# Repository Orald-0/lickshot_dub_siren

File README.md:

caga solo il proj DA SBROGLIARE  il resto é vecchio

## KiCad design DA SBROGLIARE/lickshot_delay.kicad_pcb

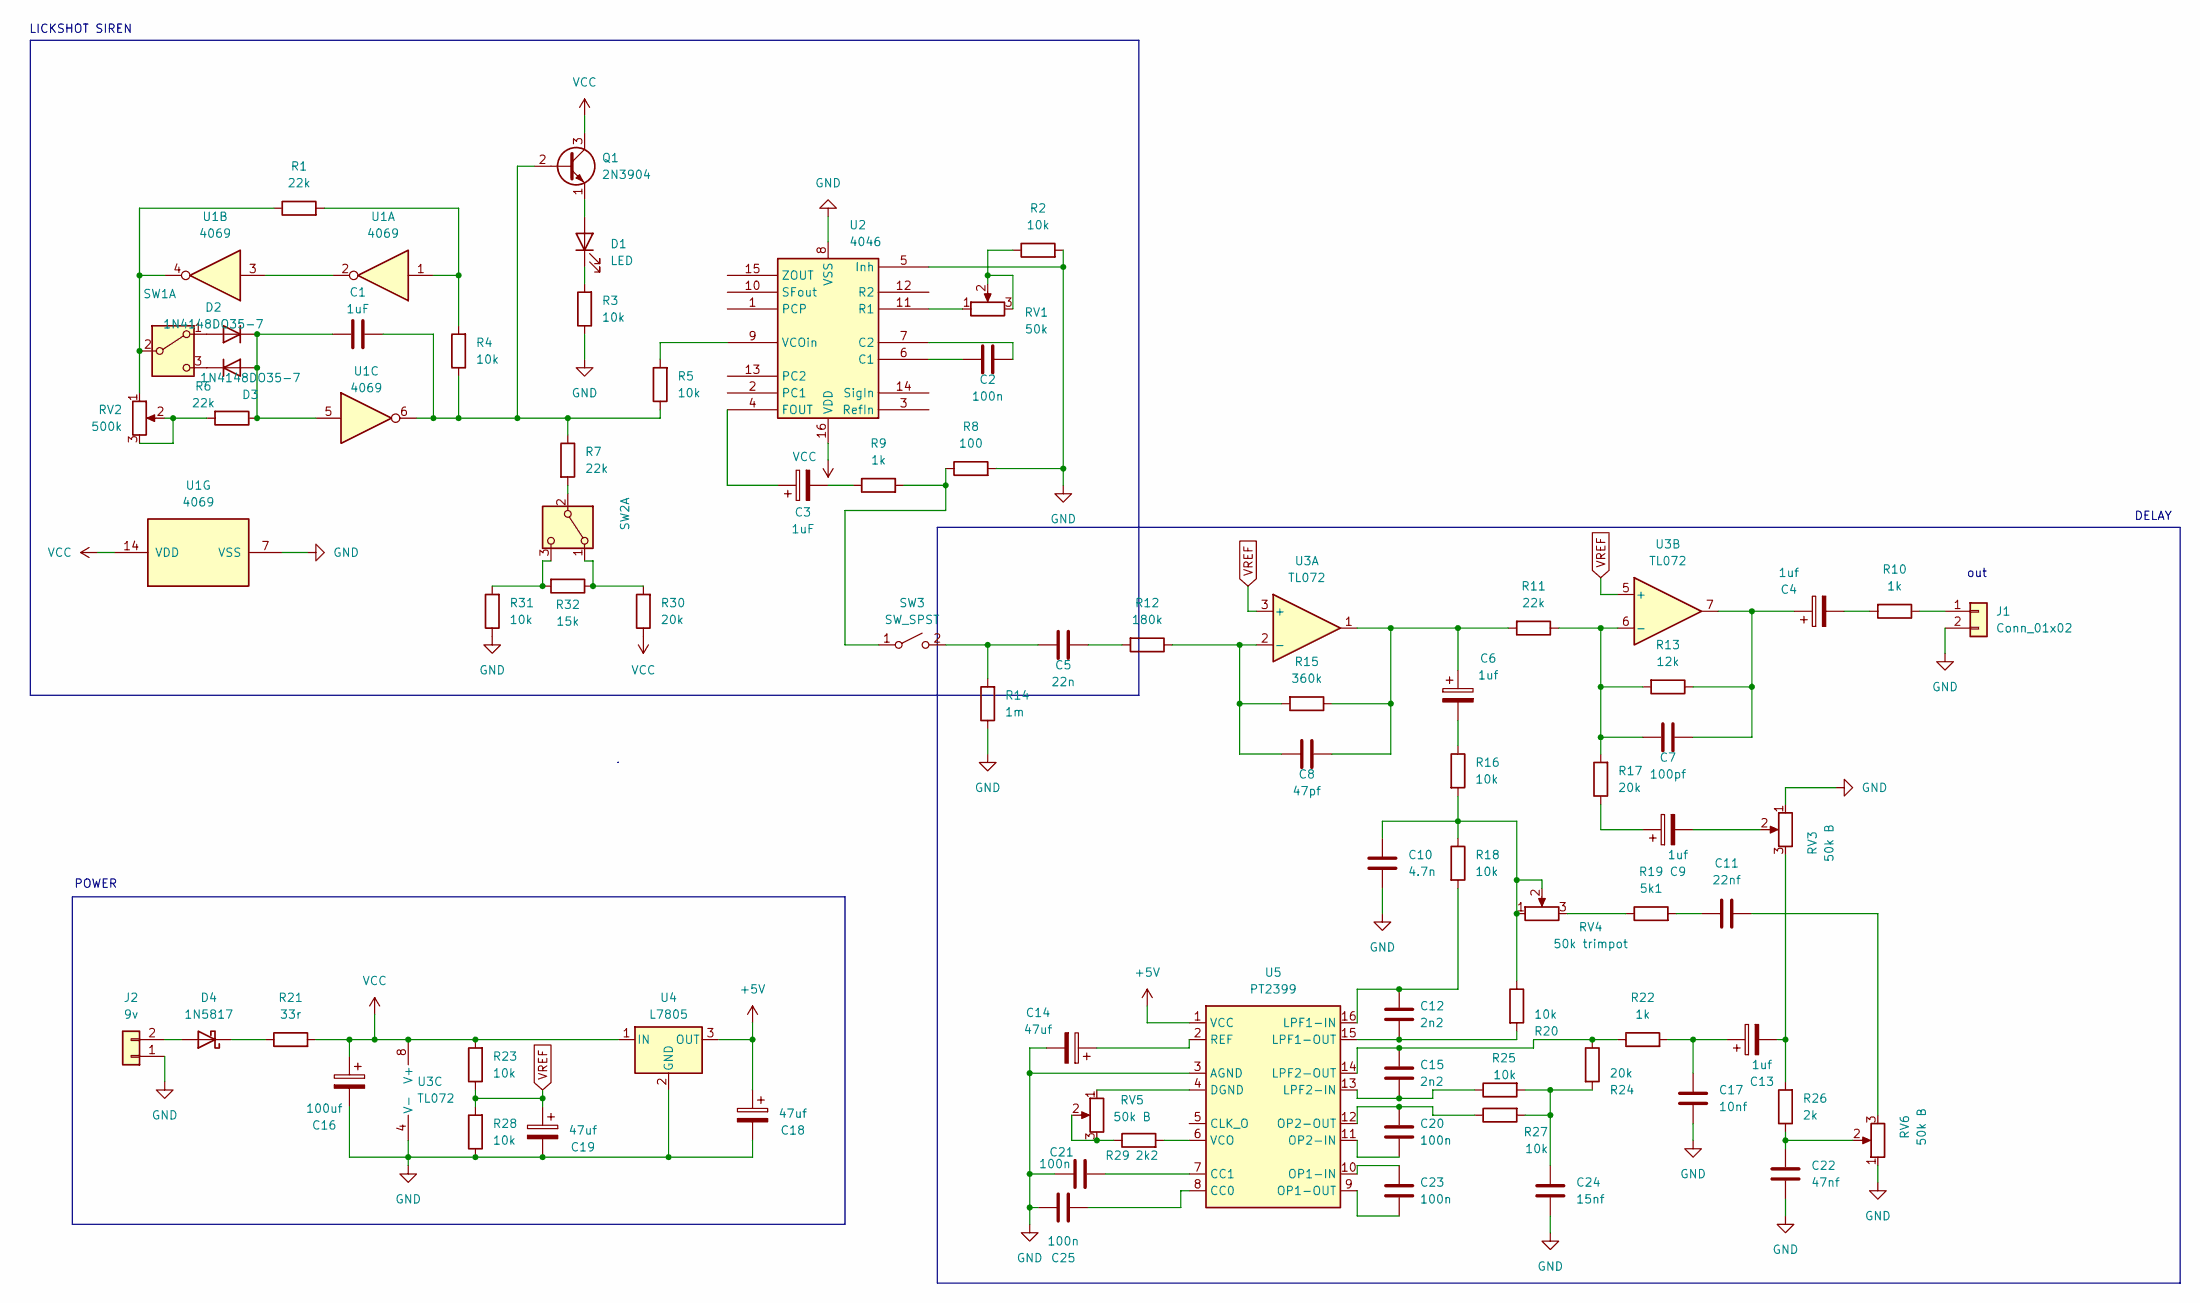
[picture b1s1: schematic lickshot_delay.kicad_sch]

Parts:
C1: 1uF; C__FILM_BOX_Rect_L7.2mm_W3mm_P5mm
C2, C20, C21, C23, C25: 100n; C__FILM_BOX_Rect_L7.2mm_W3mm_P5mm
C3: 1uF; CP_Electro_Radial_D5.0mm_P2.50mm
C4, C6, C9, C13: 1uf; CP_Electro_Radial_D5.0mm_P2.50mm
C5: 22n; C__FILM_BOX_Rect_L7.2mm_W3mm_P5mm
C7: 100pf; C__FILM_BOX_Rect_L7.2mm_W3mm_P5mm
C8: 47pf; C__FILM_BOX_Rect_L7.2mm_W3mm_P5mm
C10: 4.7n; C__FILM_BOX_Rect_L7.2mm_W3mm_P5mm
C11: 22nf; C__FILM_BOX_Rect_L7.2mm_W3mm_P5mm
C12, C15: 2n2; C__FILM_BOX_Rect_L7.2mm_W3mm_P5mm
C14, C18, C19: 47uf; CP_Electro_Radial_D5.0mm_P2.50mm
C16: 100uf; CP_Electro_Radial_D5.0mm_P2.50mm
C17: 10nf; C__FILM_BOX_Rect_L7.2mm_W3mm_P5mm
C22: 47nf; C__FILM_BOX_Rect_L7.2mm_W3mm_P5mm
C24: 15nf; C__FILM_BOX_Rect_L7.2mm_W3mm_P5mm
D1: LED; LED_D5.0mm
D2, D3: 1N4148DO35-7; DIODE_DO-35_SOD27_P7.62mm_Horizontal
D4: 1N5817; DIODE_DO-35_SOD27_P7.62mm_Horizontal
J1: Conn_01x02; SolderWire-0.5sqmm_1x02_P4.6mm_D0.9mm_OD2.1mm
J2: 9v; SolderWire-0.5sqmm_1x02_P4.6mm_D0.9mm_OD2.1mm
Q1: 2N3904; TO-92_Inline
R1, R6, R7, R11: 22k; RES_0.25watt_L3.6mm_D1.6mm_P7.62mm_Horizontal
R2, R3, R4, R5, R16, R18, R20, R23, R25, R27, R28, R31: 10k; RES_0.25watt_L3.6mm_D1.6mm_P7.62mm_Horizontal
R8: 100; RES_0.25watt_L3.6mm_D1.6mm_P7.62mm_Horizontal
R9, R10, R22: 1k; RES_0.25watt_L3.6mm_D1.6mm_P7.62mm_Horizontal
R12: 180k; RES_0.25watt_L3.6mm_D1.6mm_P7.62mm_Horizontal
R13: 12k; RES_0.25watt_L3.6mm_D1.6mm_P7.62mm_Horizontal
R14: 1m; RES_0.25watt_L3.6mm_D1.6mm_P7.62mm_Horizontal
R15: 360k; RES_0.25watt_L3.6mm_D1.6mm_P7.62mm_Horizontal
R17, R24, R30: 20k; RES_0.25watt_L3.6mm_D1.6mm_P7.62mm_Horizontal
R19: 5k1; RES_0.25watt_L3.6mm_D1.6mm_P7.62mm_Horizontal
R21: 33r; RES_0.25watt_L3.6mm_D1.6mm_P7.62mm_Horizontal
R26: 2k; RES_0.25watt_L3.6mm_D1.6mm_P7.62mm_Horizontal
R29: 2k2; RES_0.25watt_L3.6mm_D1.6mm_P7.62mm_Horizontal
R32: 15k; RES_0.25watt_L3.6mm_D1.6mm_P7.62mm_Horizontal
RV1: 50k; SolderWire-0.5sqmm_1x03_P4.6mm_D0.9mm_OD2.1mm
RV2: 500k; SolderWire-0.5sqmm_1x03_P4.6mm_D0.9mm_OD2.1mm
RV3, RV5, RV6: 50k B; SolderWire-0.5sqmm_1x03_P4.6mm_D0.9mm_OD2.1mm
RV4: 50k trimpot; Potentiometer_Piher_PT-10-V10_Vertical
SW1, SW2: SW_DPDT_x2; SolderWire-0.5sqmm_1x03_P4.6mm_D0.9mm_OD2.1mm
SW3: SW_SPST; SolderWire-0.5sqmm_1x02_P4.6mm_D0.9mm_OD2.1mm
U1: 4069; DIP-14_W7.62mm
U2: 4046; DIP-16_W7.62mm
U3: TL072; DIP-8_W7.62mm
U4: L7805; TO-220-3_Vertical
U5: PT2399; DIP-16_W7.62mm

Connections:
+5V: C18.1, U4.3 (OUT), U5.1 (VCC)
GND: C10.2, C14.2, C16.2, C17.1, C18.2, C19.2, C21.1, C22.2, C24.1, C25.1, J1.2, J2.1, R2.2, R3.1, R8.2, R14.1, R28.1, R31.1, RV3.1, RV6.1, U1.7 (VSS), U2.5 (Inh), U2.8 (VSS), U3.4 (V-), U4.2 (GND), U5.3 (AGND)
unnamed: C3.2, R9.1
unnamed: C4.1, C7.2, R13.1, U3.7
unnamed: C4.2, R10.2
unnamed: C5.2, R12.2
unnamed: C6.1, C8.2, R11.2, R15.1, U3.1
unnamed: C6.2, R16.1
unnamed: C9.1, R17.1
unnamed: C9.2, RV3.2
unnamed: C10.1, R16.2, R18.1, R20.1, RV4.1, RV4.2
unnamed: C11.1, R19.2
unnamed: C11.2, RV6.3
unnamed: C13.1, C17.2, R22.2
unnamed: C13.2, R26.2, RV3.3
unnamed: C22.1, R26.1, RV6.2
unnamed: C24.2, R24.2, R25.2, R27.2
unnamed: D1.2 (A), Q1.1 (E)
unnamed: D1.1 (K), R3.2
unnamed: D2.2 (A), SW1.1 (A)
unnamed: C1.1, D2.1 (K), D3.2 (A), R6.1, U1.5
unnamed: D3.1 (K), SW1.3 (C)
unnamed: D4.2 (A), J2.2
unnamed: D4.1 (K), R21.1
unnamed: J1.1, R10.1
unnamed: C1.2, Q1.2 (B), R4.1, R5.1, R7.1, U1.6
unnamed: R1.2, R4.2, U1.1
unnamed: R2.1, RV1.2, RV1.3
unnamed: R6.2, RV2.2, RV2.3
unnamed: R19.1, RV4.3
unnamed: R29.1, RV5.2, RV5.3
unnamed: R1.1, RV2.1, SW1.2 (B), U1.4
unnamed: R30.2, R32.1, SW2.1 (A)
unnamed: R7.2, SW2.2 (B)
unnamed: R31.2, R32.2, SW2.3 (C)
unnamed: R8.1, R9.2, SW3.1 (A)
unnamed: C5.1, R14.2, SW3.2 (B)
unnamed: U1.2, U1.3
unnamed: C2.1, U2.6 (C1)
unnamed: C2.2, U2.7 (C2)
unnamed: C3.1, U2.4 (FOUT)
unnamed: RV1.1, U2.11 (R1)
unnamed: R5.2, U2.9 (VCOin)
unnamed: C8.1, R12.1, R15.2, U3.2 (-)
unnamed: C7.1, R11.1, R13.2, R17.2, U3.6 (-)
unnamed: C25.2, U5.8 (CC0)
unnamed: C21.2, U5.7 (CC1)
unnamed: RV5.1, U5.4 (DGND)
unnamed: C12.1, R18.2, U5.16 (LPF1-IN)
unnamed: C12.2, R20.2, U5.15 (LPF1-OUT)
unnamed: C15.2, R25.1, U5.13 (LPF2-IN)
unnamed: C15.1, R22.1, R24.1, U5.14 (LPF2-OUT)
unnamed: C23.1, U5.10 (OP1-IN)
unnamed: C23.2, U5.9 (OP1-OUT)
unnamed: C20.2, U5.11 (OP2-IN)
unnamed: C20.1, R27.1, U5.12 (OP2-OUT)
unnamed: C14.1, U5.2 (REF)
unnamed: R29.2, U5.6 (VCO)
VCC: C16.1, Q1.3 (C), R21.2, R23.2, R30.1, U1.14 (VDD), U2.16 (VDD), U3.8 (V+), U4.1 (IN)
VREF: C19.1, R23.1, R28.2, U3.3 (+), U3.5 (+)

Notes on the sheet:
DELAY
POWER
out
LICKSHOT SIREN

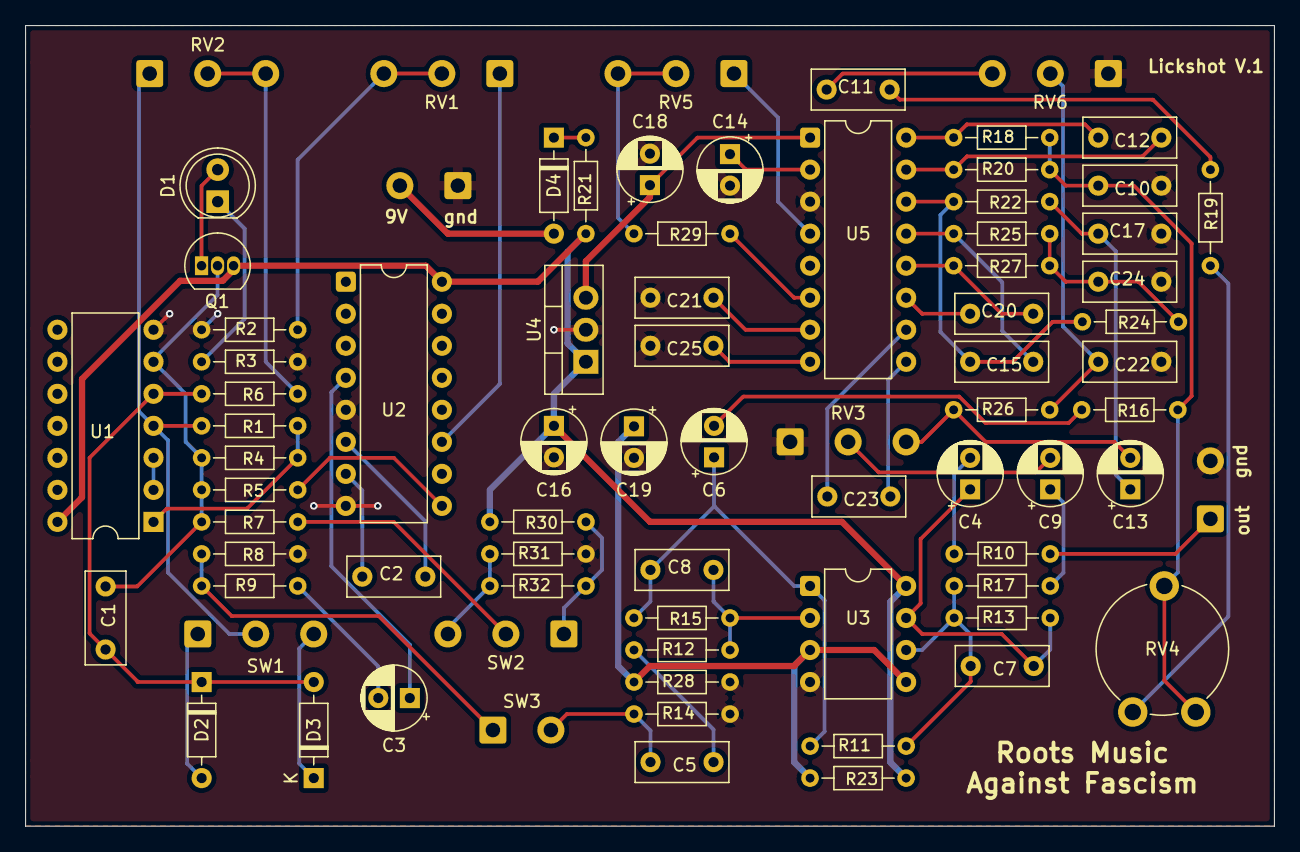
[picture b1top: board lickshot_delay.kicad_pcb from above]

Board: 2 copper layers, 99.1 x 63.5 mm, 78 parts (0 on the bottom side), 60 nets.

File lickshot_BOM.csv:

Reference,Qty,Value
"C1,C3",2,1uF
"C2,C20,C21,C23,C25",5,100nf
"C4,C6,C9,C13",4,1uf
C5,1,22nf
C7,1,100pf
C8,1,47pf
"C10,C22",2,47nf
C11,1,22nf
"C12,C15",2,2n2
"C14,C18,C19",3,47uf
C16,1,100uf
C17,1,10nf
C24,1,15nf
D1,1,LED
"D2,D3",2,1N4148DO35-7
D4,1,1N5817
Q1,1,2N3904
"R1,R6,R7,R11",4,22k
"R2,R3,R4,R5,R16,R18,R20,R23,R25,R27,R28",11,10k
R8,1,100
"R9,R10,R22",3,1k
R12,1,180k
R13,1,12k
R14,1,1m
R15,1,360k
"R17,R24",2,20k
R19,1,5k1
R21,1,33r
R26,1,2k
R29,1,2k2
RV1,1,50k
RV2,1,500k
"RV3,RV4,RV5,RV6",4,50k B
"SW1,SW2",2,SW_DPDT_x2
U1,1,4069
U2,1,4046
U3,1,TL072
U4,1,L7805
U5,1,PT2399
